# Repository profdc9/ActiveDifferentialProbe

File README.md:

This is an Active RF Differential Probe based on a cheaply available 2SC3356 Bipolar Transistor by Daniel L. Marks, KW4TI.  Dual gate Mosfets are getting hard to find, so this is what I suggest as an alternative.

The bandwidth is approximately 1 GHz (-3 dB) with 6 dB gain at low frequency.

The PCB design is distributed under the Creative Commons Shared Alike Attribution (CC-BY-SA 4.0) license.

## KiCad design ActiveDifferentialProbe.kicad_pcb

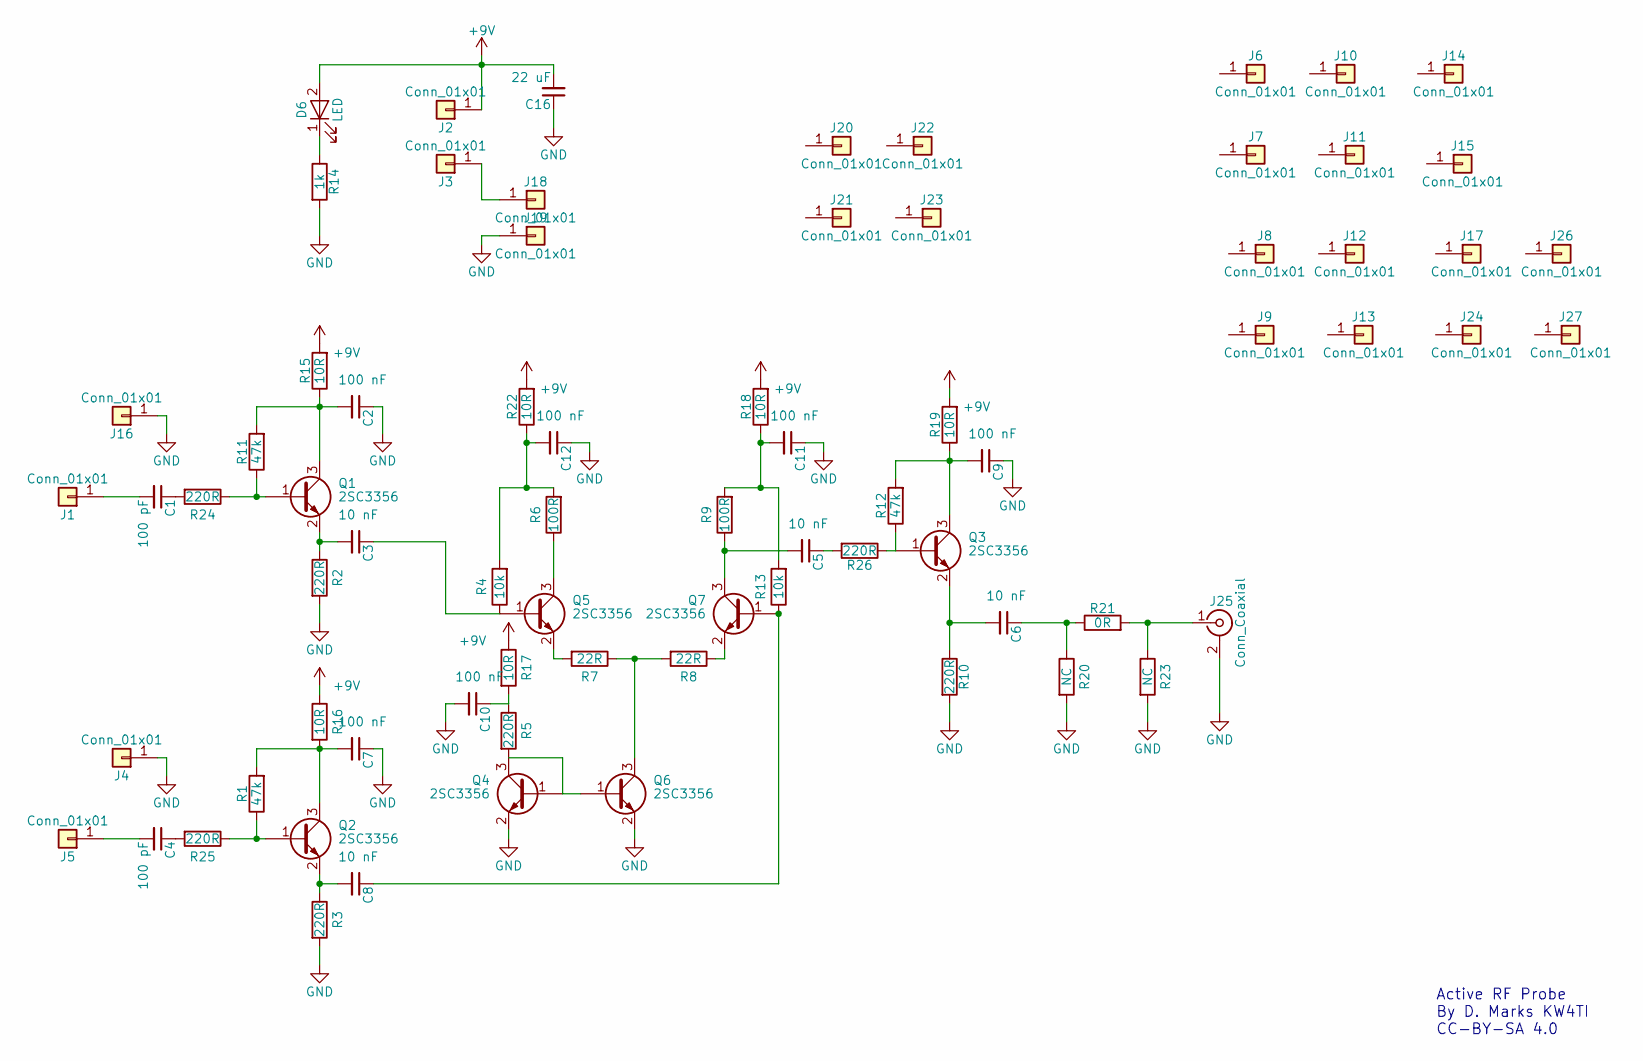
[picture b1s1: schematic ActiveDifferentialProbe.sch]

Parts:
C1, C4: 100 pF; C_0805_HandSoldering; LCSC C1790
C2, C7, C9, C10, C11, C12: 100 nF; C_0805_HandSoldering; LCSC C49678
C3, C5, C6, C8: 10 nF; C_0805_HandSoldering; LCSC C1710
C16: 22 uF; C_0805_HandSoldering; LCSC C45783
D6: LED; LED_0805_HandSoldering; LCSC C2296
J1, J2, J3, J4, J5, J16, J18, J19: Conn_01x01; PadHole
J6, J7, J8, J9, J10, J11, J12, J13, J14, J15, J17, J20, J21, J22, J23, J24, J26, J27: Conn_01x01; BigSlot
J25: Conn_Coaxial; Amphenol_RF_SMA_132289
Q1, Q2, Q3, Q4, Q5, Q6, Q7: 2SC3356; SOT-23; LCSC C9659
R1, R11, R12: 47k; R_0805_HandSoldering; LCSC C17713
R2, R3, R5, R10, R24, R25, R26: 220R; R_0805_HandSoldering; LCSC C17557
R4, R13: 10k; R_0805_HandSoldering; LCSC C17414
R6, R9: 100R; R_0805_HandSoldering; LCSC C17408
R7, R8: 22R; R_0805_HandSoldering; LCSC C17561
R14: 1k; R_0805_HandSoldering; LCSC C17513
R15, R16, R17, R18, R19, R22: 10R; R_0805_HandSoldering; LCSC C17415
R20, R23: NC; R_0805_HandSoldering
R21: 0R; R_0805_HandSoldering; LCSC C17477

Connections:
+9V: C16.2, D6.2 (A), J2.1, R15.2, R16.1, R17.1, R18.2, R19.2, R22.2
GND: C2.1, C7.1, C9.1, C10.2, C11.1, C12.1, C16.1, J4.1, J16.1, J19.1, J25.2 (Ext), Q4.2 (E), Q6.2 (E), R2.2, R3.2, R10.2, R14.2, R20.2, R23.2
unnamed: C1.1, R24.2
unnamed: C1.2, J1.1
unnamed: C2.2, Q1.3 (C), R11.2, R15.1
unnamed: C3.1, Q5.1 (B), R4.1
unnamed: C3.2, Q1.2 (E), R2.1
unnamed: C4.1, R25.2
unnamed: C4.2, J5.1
unnamed: C5.1, R26.2
unnamed: C5.2, Q7.3 (C), R9.1
unnamed: C6.1, R20.1, R21.1
unnamed: C6.2, Q3.2 (E), R10.1
unnamed: C7.2, Q2.3 (C), R1.2, R16.2
unnamed: C8.1, Q7.1 (B), R13.1
unnamed: C8.2, Q2.2 (E), R3.1
unnamed: C9.2, Q3.3 (C), R12.2, R19.1
unnamed: C10.1, R5.1, R17.2
unnamed: C11.2, R9.2, R13.2, R18.1
unnamed: C12.2, R4.2, R6.2, R22.1
unnamed: D6.1 (K), R14.1
unnamed: J3.1, J18.1
unnamed: J25.1 (In), R21.2, R23.1
unnamed: Q1.1 (B), R11.1, R24.1
unnamed: Q2.1 (B), R1.1, R25.1
unnamed: Q3.1 (B), R12.1, R26.1
unnamed: Q4.1 (B), Q4.3 (C), Q6.1 (B), R5.2
unnamed: Q5.2 (E), R7.2
unnamed: Q5.3 (C), R6.1
unnamed: Q6.3 (C), R7.1, R8.2
unnamed: Q7.2 (E), R8.1

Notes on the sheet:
Active RF Probe By D. Marks KW4TI CC-BY-SA 4.0

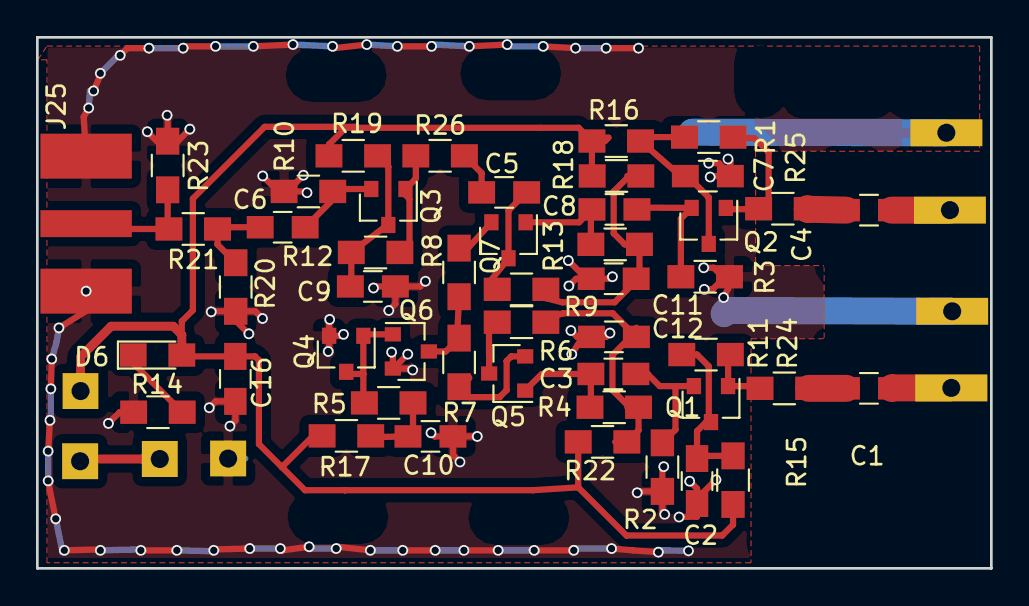
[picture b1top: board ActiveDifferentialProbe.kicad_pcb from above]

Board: 2 copper layers, 53.0 x 29.5 mm, 74 parts (0 on the bottom side), 31 nets.

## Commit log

2020-04-22 Added LCSC parts, fixed symbol, added decoupling resistors
2020-04-23 Changed to 2SC3356
2020-04-29 Added LCSC part numbers, added cutout notched, added series base resistors to emitter followers
